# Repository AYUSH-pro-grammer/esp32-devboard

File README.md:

# ESP32-S2 Development Board

Development board built using Espressif ESP32-S2FH4 with USB-C, two WS2812B LEDs, 3.3V LDO and GPIO headers, which have 15 pins on both sides.

## Reasons for creating this project

I created this board because I want to get experience in designing a PCB and build my own ESP32 board. I was interested in building the schematic, routing the PCB and putting everything together.

### How it works

The board receives 5V from USB-C port and uses 3.3V LDO to power the ESP32-S2 module.
The ESP32-S2 is the core part of the board and can be programmed through USB-C.
GPIO pins are routed to two 1x15 headers to use them with jumper wires and breadboard.
WS2812B LEDs and a button were used to add some functionality to the board.

### 3D Model

### Schematics & Routing

## BOM Summary

| Qty | Component                  | Selected Part                             | Supplier                  | Link                                                            | MOQ | Unit Price (USD) | Order Cost (USD) |
| --: | -------------------------- | ----------------------------------------- | ------------------------- | --------------------------------------------------------------- | --: | ---------------: | ---------------: |
|   1 | 25 MHz Crystal, 20 pF      | SJK 7F25000E20UCG                         | SJK                       | [C252274](https://www.lcsc.com/product-detail/C252274.html)     |   5 |          $0.1139 |            $0.57 |
|   2 | 33 pF Capacitor            | FOJAN FCC0402N330J500AT                   | FOJAN                     | [C5137486](https://www.lcsc.com/product-detail/C5137486.html)   | 100 |          $0.0030 |            $0.30 |
|   1 | 100 nF Capacitor           | Samsung Electro-Mechanics CL05B104KO5NNNC | Samsung Electro-Mechanics | [C1525](https://www.lcsc.com/product-detail/C1525.html)         | 100 |          $0.0046 |            $0.46 |
|   7 | 1 µF Capacitor             | Samsung Electro-Mechanics CL05A105KA5NQNC | Samsung Electro-Mechanics | [C52923](https://www.lcsc.com/product-detail/C52923.html)       |  50 |          $0.0100 |            $0.50 |
|   2 | 4.7 µF Capacitor           | Samsung Electro-Mechanics CL05A475MP5NRNC | Samsung Electro-Mechanics | [C23733](https://www.lcsc.com/product-detail/C23733.html)       |  50 |          $0.0167 |            $0.84 |
|   2 | WS2812B-2020 LED           | XINGLIGHT XL-2020RGBC-2812B               | XINGLIGHT                 | [C5349955](https://www.lcsc.com/product-detail/C5349955.html)   |   5 |          $0.1112 |            $0.56 |
|   1 | 1 A / 12 V Resettable Fuse | R+O SMD0805-100-12                        | R+O                       | [C46640991](https://www.lcsc.com/product-detail/C46640991.html) |  10 |          $0.0435 |            $0.44 |
|   1 | USB-C Receptacle           | SHOU HAN TYPE-C16PIN                      | SHOU HAN                  | [C393939](https://www.lcsc.com/product-detail/C393939.html)     |  10 |          $0.0592 |            $0.59 |
|   5 | 5.1 kΩ Resistor            | UNI-ROYAL 0402WGF5101TCE                  | UNI-ROYAL                 | [C25905](https://www.lcsc.com/product-detail/C25905.html)       | 100 |          $0.0023 |            $0.23 |
|   3 | 10 kΩ Resistor             | UNI-ROYAL 0402WGF1002TCE                  | UNI-ROYAL                 | [C25744](https://www.lcsc.com/product-detail/C25744.html)       | 100 |          $0.0034 |            $0.34 |
|   1 | Tactile Push Button        | XUNPU TS-1088-AR02016                     | XUNPU                     | [C720477](https://www.lcsc.com/product-detail/C720477.html)     |  10 |          $0.0516 |            $0.52 |
|   1 | ESP32-S2FH4                | ESPRESSIF ESP32-S2FH4                     | ESPRESSIF                 | [C2840995](https://www.lcsc.com/product-detail/C2840995.html)   |   1 |          $2.4574 |            $2.46 |
|   1 | 3.3 V LDO                  | TOREX XC6206P332MR-G                      | TOREX                     | [C5446](https://www.lcsc.com/product-detail/C5446.html)         |   5 |          $0.1437 |            $0.72 |

## Total

** BOM Total: $8.53 USD**

## Parts

| Designator                 | Part                |
| -------------------------- | ------------------- |
| C1, C2                     | 33 pF               |
| C3, C4, C5, C6, C7, C8, C9 | 1 µF                |
| C10                        | 100 nF              |
| C39, C40                   | 4.7 µF              |
| D1, D2                     | WS2812B-2020        |
| F1                         | Resettable Fuse     |
| J1                         | USB-C Receptacle    |
| R1, R2, R3, R4, R5         | 5.1 kΩ              |
| R6, R7, R8                 | 10 kΩ               |
| SW1                        | Tactile Push Button |
| U1                         | ESP32-S2FH4         |
| U2                         | XC6206P332MR-G      |
| Y1                         | 25 MHz Crystal      |

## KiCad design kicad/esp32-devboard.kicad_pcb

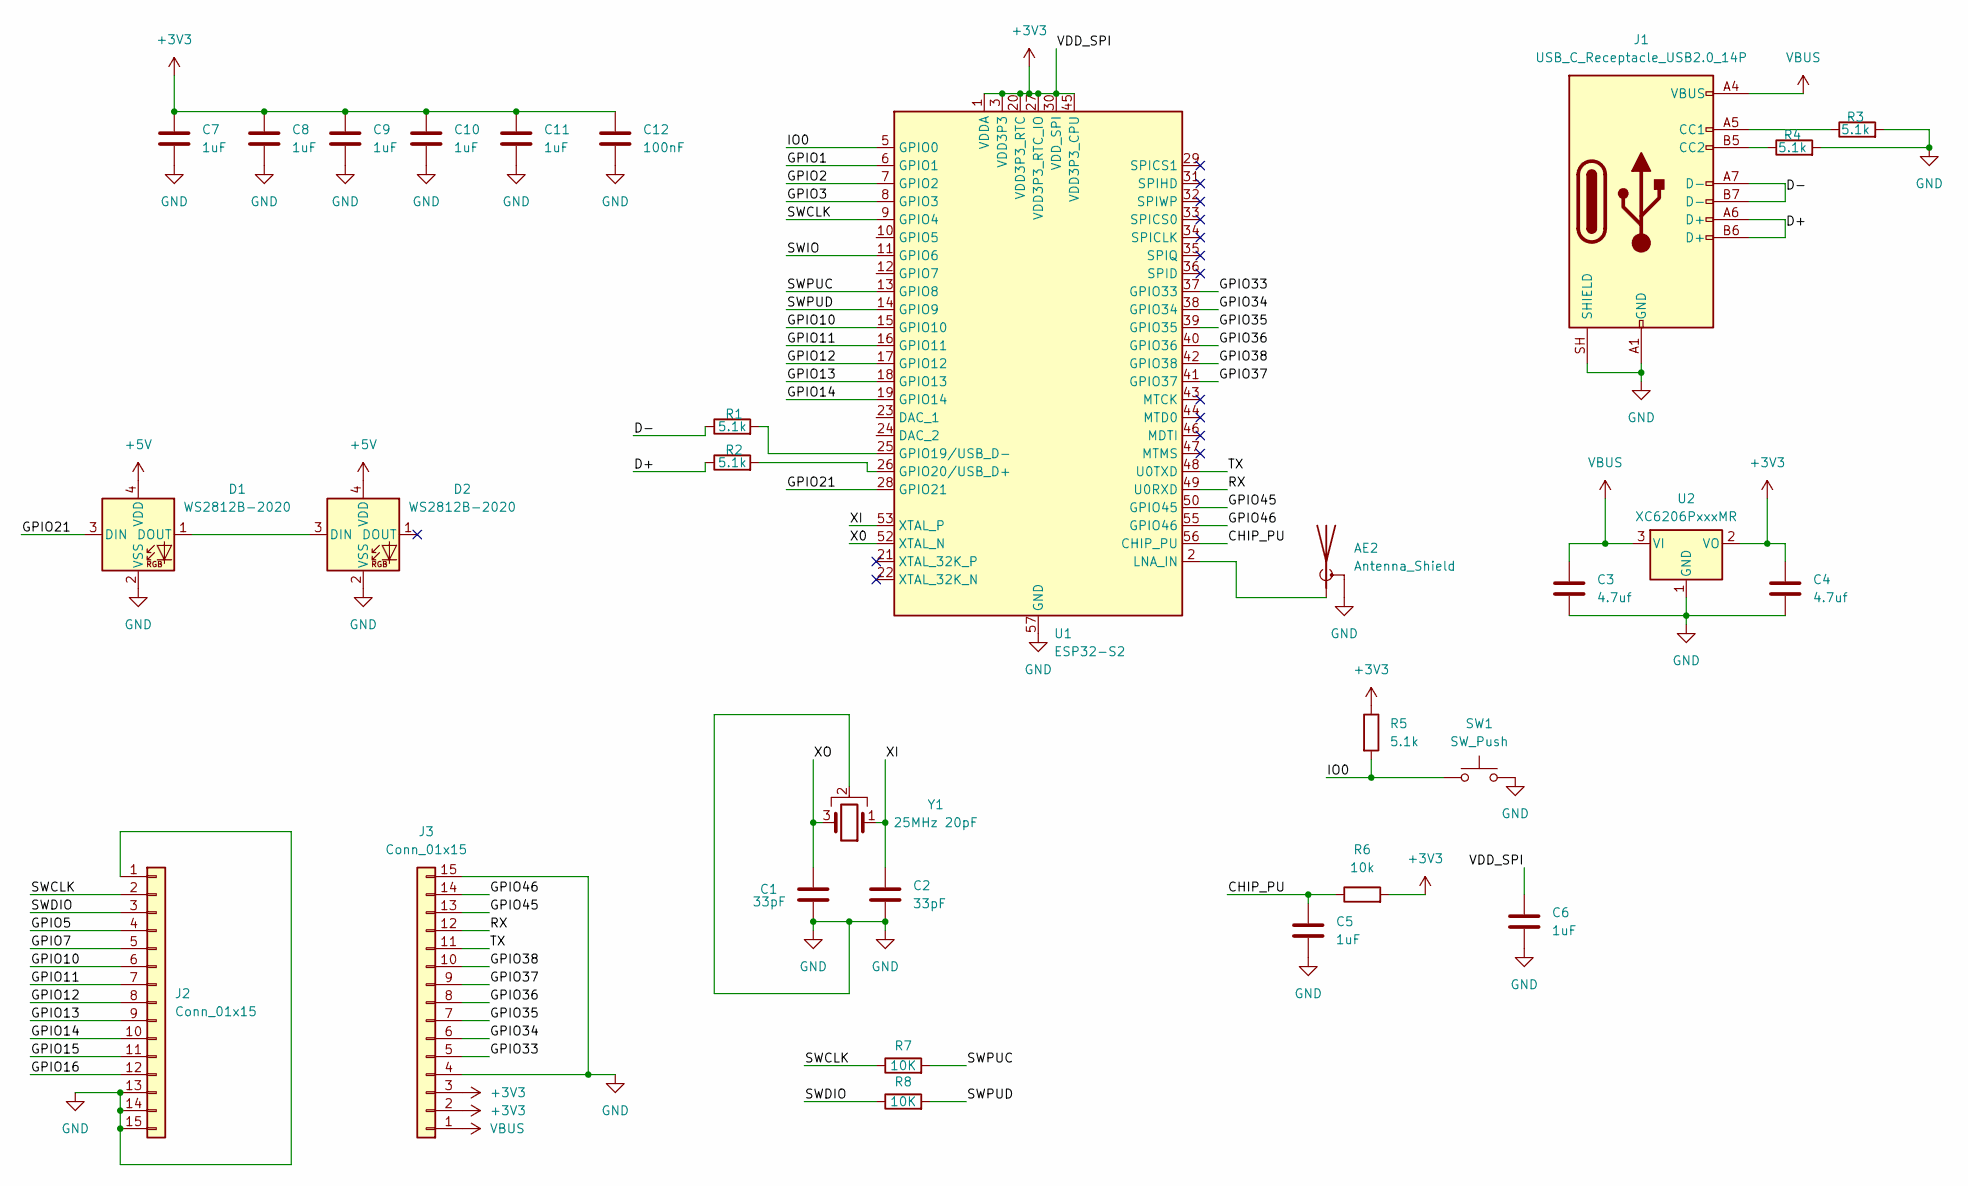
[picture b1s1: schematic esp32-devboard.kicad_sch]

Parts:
AE2: Antenna_Shield; Texas_SWRA117D_2.4GHz_Left
C1, C2: 33pF; C_0402_1005Metric
C3, C4: 4.7uf; C_0402_1005Metric
C5, C6, C7, C8, C9, C10, C11: 1uF; C_0402_1005Metric
C12: 100nF; C_0402_1005Metric
D1, D2: WS2812B-2020; LED_WS2812B-2020_PLCC4_2.0x2.0mm
J1: USB_C_Receptacle_USB2.0_14P; USB_C_Receptacle_HRO_TYPE-C-31-M-12
J2, J3: Conn_01x15; PinHeader_1x15_P2.54mm_Vertical
R1, R2, R3, R4, R5: 5.1k; R_0402_1005Metric
R6: 10k; R_0402_1005Metric
R7, R8: 10K; R_0402_1005Metric
SW1: SW_Push; SW_PUSH_6mm
U1: ESP32-S2; QFN-56-1EP_7x7mm_P0.4mm_EP4x4mm
U2: XC6206PxxxMR; SOT-23-3
Y1: 25MHz 20pF; Crystal_SMD_2016-4Pin_2.0x1.6mm

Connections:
+3V3: C4.1, C6.1, C7.1, C8.1, C9.1, C10.1, C11.1, C12.1, J3.2, J3.3, R5.1, R6.2, U1.1 (VDDA), U1.3 (VDD3P3), U1.4 (VDD3P3), U1.20 (VDD3P3_RTC), U1.27 (VDD3P3_RTC_IO), U1.30 (VDD_SPI), U1.45 (VDD3P3_CPU), U1.51 (VDDA), U1.54 (VDDA), U2.2 (VO)
+5V: D1.4 (VDD), D2.4 (VDD)
/CHIP_PU: C5.1, R6.1, U1.56 (CHIP_PU)
/D+: J1.A6 (D+), J1.B6 (D+), R2.1
/D-: J1.A7 (D-), J1.B7 (D-), R1.1
/GPIO1: U1.6 (GPIO1)
/GPIO2: U1.7 (GPIO2)
/GPIO3: U1.8 (GPIO3)
/GPIO5: J2.4
/GPIO7: J2.5
/GPIO10: J2.6, U1.15 (GPIO10)
/GPIO11: J2.7, U1.16 (GPIO11)
/GPIO12: J2.8, U1.17 (GPIO12)
/GPIO13: J2.9, U1.18 (GPIO13)
/GPIO14: J2.10, U1.19 (GPIO14)
/GPIO15: J2.11
/GPIO16: J2.12
/GPIO21: D1.3 (DIN), U1.28 (GPIO21)
/GPIO33: J3.5, U1.37 (GPIO33)
/GPIO34: J3.6, U1.38 (GPIO34)
/GPIO35: J3.7, U1.39 (GPIO35)
/GPIO36: J3.8, U1.40 (GPIO36)
/GPIO37: J3.9, U1.41 (GPIO37)
/GPIO38: J3.10, U1.42 (GPIO38)
/GPIO45: J3.13, U1.50 (GPIO45)
/GPIO46: J3.14, U1.55 (GPIO46)
/IO0: R5.2, SW1.1, U1.5 (GPIO0)
/RX: J3.12, U1.49 (U0RXD)
/SWCLK: J2.2, R7.1, U1.9 (GPIO4)
/SWDIO: J2.3, R8.1
/SWIO: U1.11 (GPIO6)
/SWPUC: R7.2, U1.13 (GPIO8)
/SWPUD: R8.2, U1.14 (GPIO9)
/TX: J3.11, U1.48 (U0TXD)
/X0: U1.52 (XTAL_N)
/XI: C2.1, U1.53 (XTAL_P), Y1.1
/XO: C1.1, Y1.3
GND: AE2.2 (Shield), C1.2, C2.2, C3.2, C4.2, C5.2, C6.2, C7.2, C8.2, C9.2, C10.2, C11.2, C12.2, D1.2 (VSS), D2.2 (VSS), J1.A1 (GND), J1.A12 (GND), J1.B1 (GND), J1.B12 (GND), J1.SH (SHIELD), J2.1, J2.13, J2.14, J2.15, J3.4, J3.15, R3.2, R4.2, SW1.2, U1.57 (GND), U2.1 (GND), Y1.2
unnamed: AE2.1 (A), U1.2 (LNA_IN)
unnamed: D1.1 (DOUT), D2.3 (DIN)
unnamed: J1.A5 (CC1), R3.1
unnamed: J1.B5 (CC2), R4.1
unnamed: R1.2, U1.25 (GPIO19/USB_D-)
unnamed: R2.2, U1.26 (GPIO20/USB_D+)
VBUS: C3.1, J1.A4 (VBUS), J1.A9 (VBUS), J1.B4 (VBUS), J1.B9 (VBUS), J3.1, U2.3 (VI)

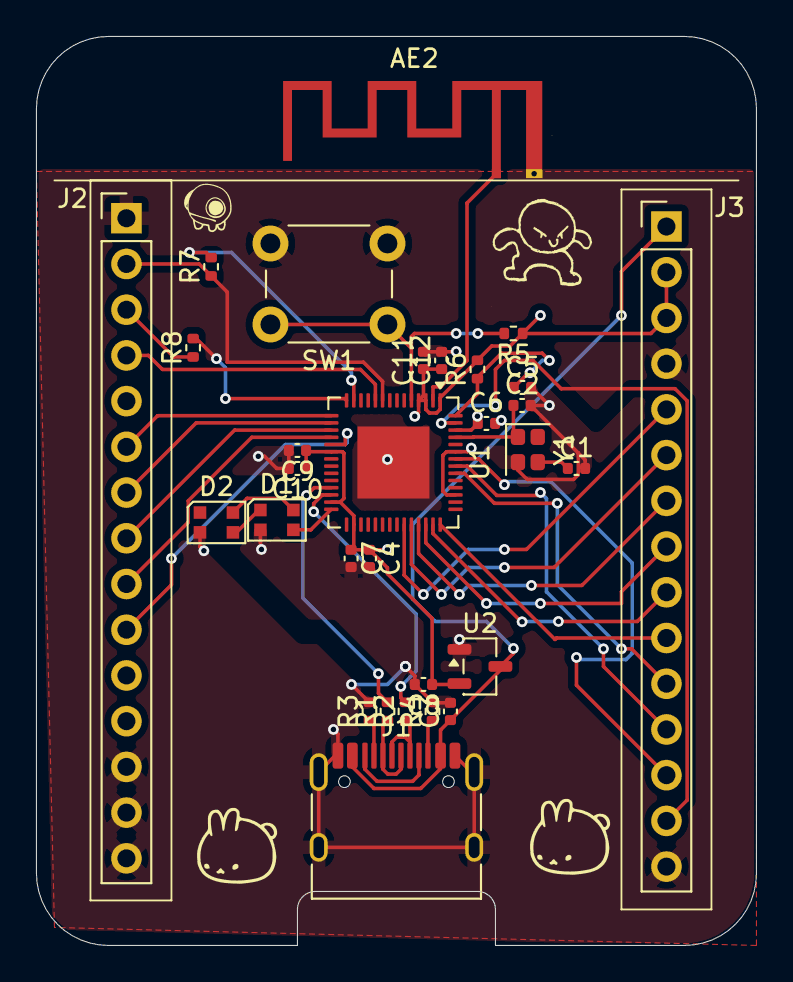
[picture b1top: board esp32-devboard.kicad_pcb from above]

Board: 4 copper layers, 40.0 x 50.5 mm, 30 parts (0 on the bottom side), 36 nets.
